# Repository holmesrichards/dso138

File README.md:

# DSO138 Oscilloscope

This is the JYE Tech DSO138 Oscilloscope put behind a 10 cm wide Kosmo format panel. 

Slide switches, tactile buttons, and trigger indicator LED are mounted to an auxiliary PCB mounted behind the panel. Also on this board are a Eurorack style 10-pin power header with 10 µF caps and power reversal diodes, and a 9 volt regulator and TL072 op amp with associated passive components.

A BNC jack and a 1/4" phone input jack are mounted on the front panel. A toggle switch selects whether the scope input is connected to the BNC or to the 1/4" jack signal after being buffered with the TL072. The latter signal, buffered, also goes to a second 1/4" panel mounted jack, so the signal can be passed on to another module.

Also on the front panel is another toggle switch, controlling the 9 V power. (It's good to power off the scope when not in use, for at least three reasons: the scope draws about 130 mA current on the +12 V rail, it probably puts out some digital noise you don't want getting into your synth sound, and leaving it powered off when not in use will help extend the life of the display.)

Connections to and from each slide switch are sent to the DSO138 switch footprints via an 8-conductor ribbon cable. A fourth ribbon cable connects the tactile buttons, both sides of the LED, and the input signal to the appropriate pads on the main board. Two more wires carry 9 V and ground to that board, which is mounted perpendicular to the front panel. I used a 3D printed carrier and long spacers to attach it.

The display PCB is mounted to the front panel and is connected to the main PCB via a 40 conductor ribbon cable.

## Current draw
130 mA +12 V, 10 mA -12 V

## Photos

## Documentation

* [Schematic (auxiliary board)](Docs/dso138.pdf)
* PCB layout: [front](Docs/dso138_layout_front.pdf), [back](Docs/dso138_layout_back.pdf)
* [BOM](Docs/dso138_bom.md)
* [Build notes](Docs/build.md)

## GitHub repository

* [https://github.com/holmesrichards/dso138](https://github.com/holmesrichards/dso138)

## Submodules

This repo uses submodules aoKicad and Kosmo_panel, which provide needed libaries for KiCad. To clone:

```
git clone git@github.com:holmesrichards/dso138.git
git submodule init
git submodule update
```

Alternatively do

```
git clone --recurse-submodules git@github.com:holmesrichards/dso138.git
```

Or if you download the repository as a zip file, you must also click on the "aoKicad" and "Kosmo\_panel" links on the GitHub page (they'll be in the Libraries folder and will have "@ something" after them) and download them as separate zip files which you can unzip into this repo's aoKicad and Kosmo\_panel directories (in the Libraries folder).

If desired, copy the files from aoKicad and Kosmo\_panel to wherever you prefer. 

Then in KiCad, go into Edit Symbols and add symbol libraries 

```
aoKicad/AO_symbols
Kosmo_panel/Kosmo
```
and go into Edit Footprints and add footprint libraries 
```
aoKicad/AO_tht
Kosmo_panel/Kosmo_panel.
```

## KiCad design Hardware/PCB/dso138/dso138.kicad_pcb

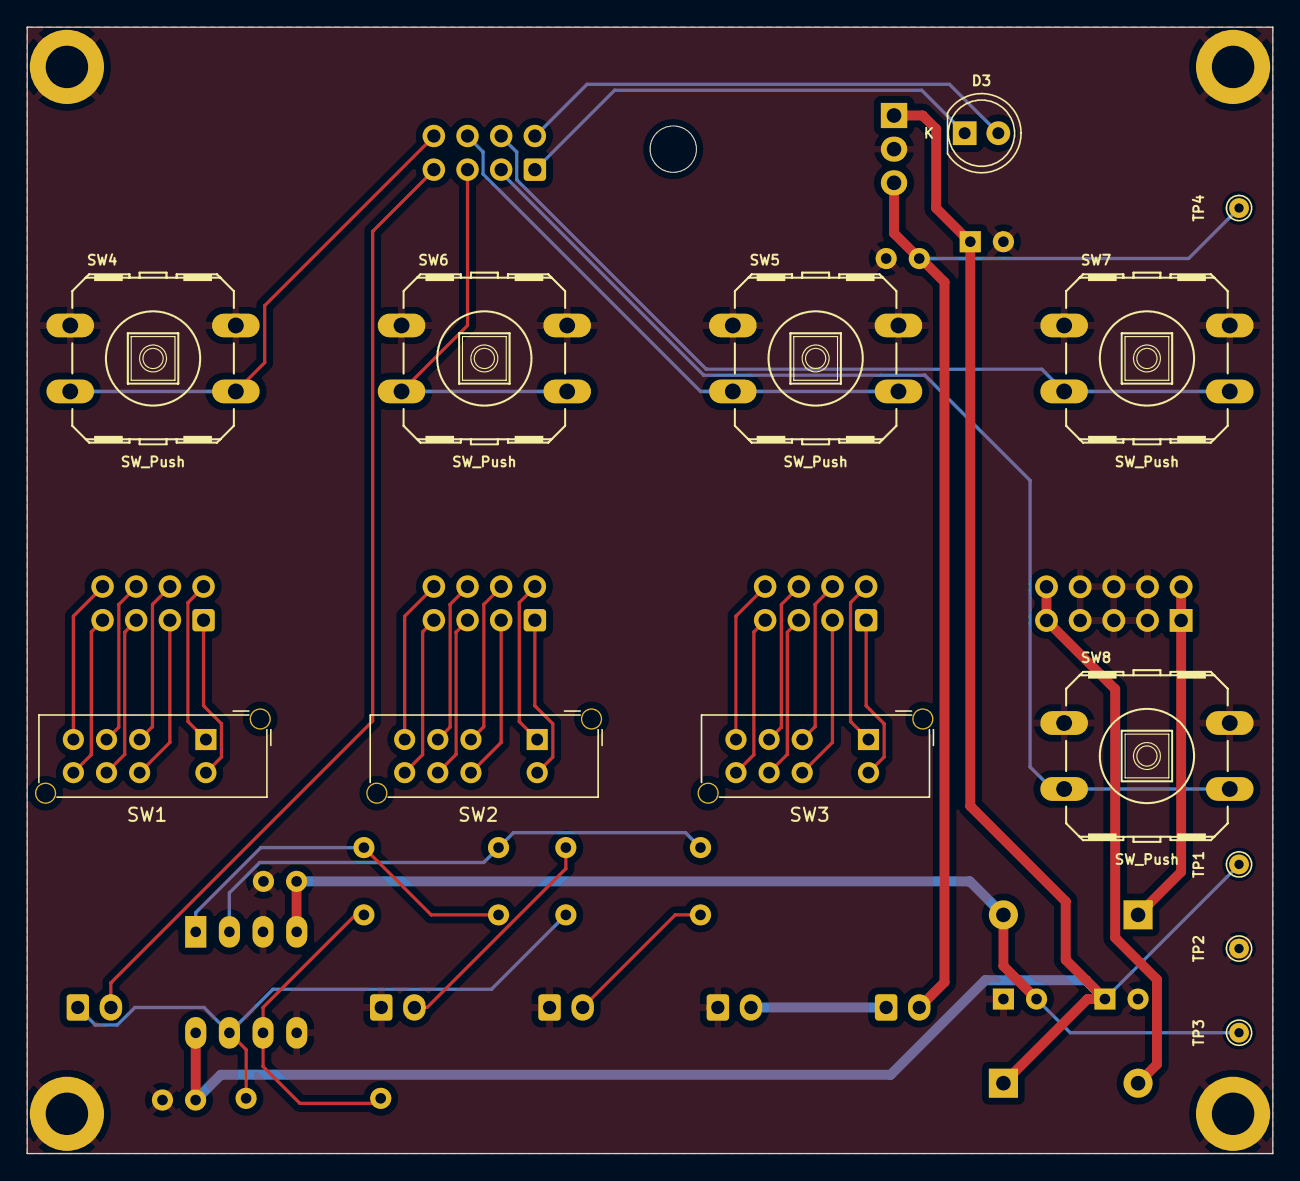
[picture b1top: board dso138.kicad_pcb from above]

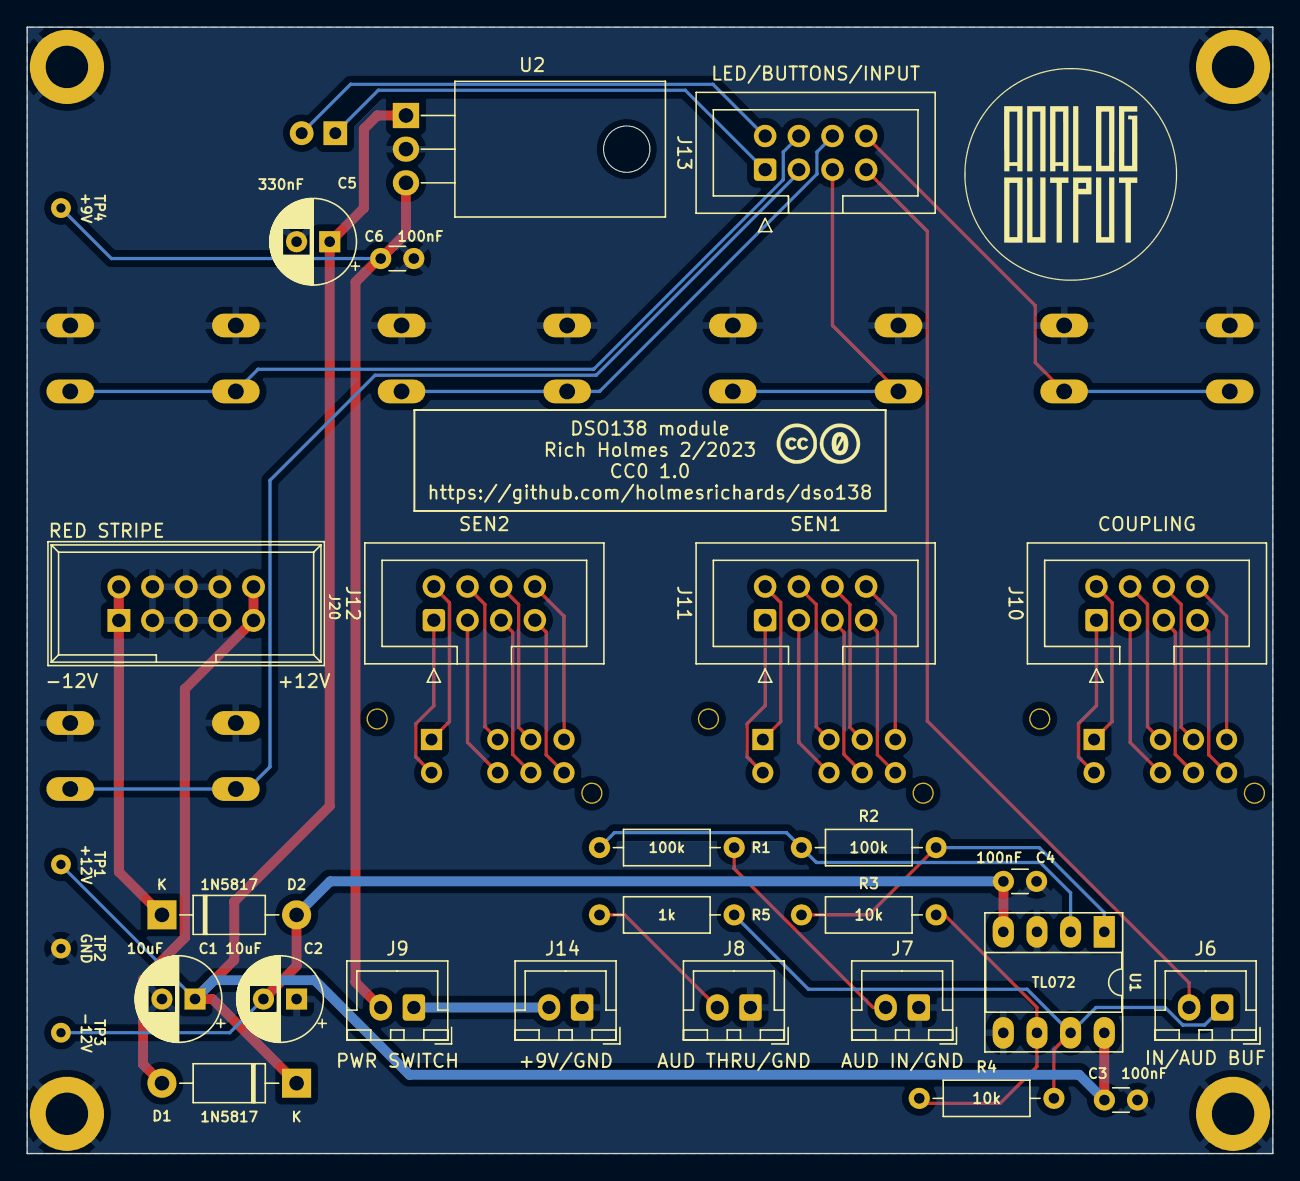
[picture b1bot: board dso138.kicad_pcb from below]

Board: 2 copper layers, 94.0 x 85.0 mm, 45 parts (27 on the bottom side), 45 nets.

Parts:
C1, C2: 10uF; CP_Radial_D6.3mm_P2.50mm
C3, C4, C6: 100nF; C_Disc_D3.0mm_W1.6mm_P2.50mm
C5: 330nF; CP_Radial_D6.3mm_P2.50mm
D1, D2: 1N5817; D_DO-41_SOD81_P10.16mm_Horizontal
D3: LED_green; LED_D5.0mm
GRAF1: Behind; dso138_behind
GRAF1#2: CC0 logo; CC0_logo
GRAF2: AO logo; analogoutput
H1, H2, H3, H4: MountingHole_with_pin; MountingHole_3.2mm_Pad
J6, J7, J8, J9, J14: Conn_01x02; JST_XH_B2B-XH-A_1x02_P2.50mm_Vertical
J10, J11, J12, J13: Conn_02x04_Odd_Even; IDC-Header_2x04_P2.54mm_Vertical
J20: Synth_power_2x5; Power_Header
R1, R2: 100k; R_Axial_DIN0207_L6.3mm_D2.5mm_P10.16mm_Horizontal
R3, R4: 10k; R_Axial_DIN0207_L6.3mm_D2.5mm_P10.16mm_Horizontal
R5: 1k; R_Axial_DIN0207_L6.3mm_D2.5mm_P10.16mm_Horizontal
SW1, SW2, SW3: SW_DP3T; SW_CK_OS203012MU5QP1_DP3T
SW4, SW5, SW6, SW7, SW8: SW_Push; Tactile_E-switch_TL1100F160Q
TP1: +12V; TestPoint_THTPad_D1.5mm_Drill0.7mm
TP2: GND; TestPoint_THTPad_D1.5mm_Drill0.7mm
TP3: -12V; TestPoint_THTPad_D1.5mm_Drill0.7mm
TP4: +9V; TestPoint_THTPad_D1.5mm_Drill0.7mm
U1: TL072; DIP-8_W7.62mm_Socket_LongPads
U2: LM7809_TO220; TO-220-3_Horizontal_TabDown

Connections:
+9V: C6.1, J9.2, TP4.1, U2.3 (VO)
+12V: C1.1, C3.1, C5.1, D1.1 (K), TP1.1, U1.8 (V+), U2.1 (VI)
-12V: C2.2, C4.2, D2.2 (A), TP3.1, U1.4 (V-)
/9V_SWITCHED: J9.1, J14.2
/AUDIO_BUF: J6.1, R4.2, R5.1, U1.7
/AUDIO_IN: J7.2, R1.1
/AUDIO_THROUGH: J8.2, R5.2
/Controls board/+12_IN: D1.2 (A), J20.9 (+12V), J20.10 (+12V)
/Controls board/-12_IN: D2.1 (K), J20.1 (-12V), J20.2 (-12V)
/INPUT: J6.2, J13.7
/LED_A: D3.2 (A), J13.2
/LED_K: D3.1 (K), J13.1
/SW_CPL_AC_A: J10.6, SW1.3
/SW_CPL_AC_B: J10.5, SW1.7
/SW_CPL_COMM_A: J10.4, SW1.2
/SW_CPL_COMM_B: J10.3, SW1.6
/SW_CPL_DC_A: J10.2, SW1.1
/SW_CPL_DC_B: J10.1, SW1.5
/SW_CPL_GND_A: J10.8, SW1.4
/SW_CPL_GND_B: J10.7, SW1.8
/SW_HOLDRUN: J13.8, SW4.2
/SW_MINUS: J13.5, SW6.2
/SW_PLUS: J13.6, SW5.2
/SW_RESET: J13.3, SW8.2
/SW_SELECT: J13.4, SW7.2
/SW_SEN1_1V_A: J11.8, SW2.4
/SW_SEN1_1V_B: J11.7, SW2.8
/SW_SEN1_10MV_A: J11.2, SW2.1
/SW_SEN1_10MV_B: J11.1, SW2.5
/SW_SEN1_100MV_A: J11.6, SW2.3
/SW_SEN1_100MV_B: J11.5, SW2.7
/SW_SEN1_COMM_A: J11.4, SW2.2
/SW_SEN1_COMM_B: J11.3, SW2.6
/SW_SEN2_COMM_A: J12.4, SW3.2
/SW_SEN2_COMM_B: J12.3, SW3.6
/SW_SEN2_X1_A: J12.2, SW3.1
/SW_SEN2_X1_B: J12.1, SW3.5
/SW_SEN2_X2_A: J12.6, SW3.3
/SW_SEN2_X2_B: J12.5, SW3.7
/SW_SEN2_X5_A: J12.8, SW3.4
/SW_SEN2_X5_B: J12.7, SW3.8
GND: C1.2, C2.1, C3.2, C4.1, C5.2, C6.2, H1.1, H2.1, H3.1, H4.1, J7.1, J8.1, J14.1, J20.3 (GND), J20.4 (GND), J20.5 (GND), J20.6 (GND), J20.7 (GND), J20.8 (GND), SW4.1, SW5.1, SW6.1, SW7.1, SW8.1, TP2.1, U1.3 (+), U1.5 (+), U2.2 (GND)
unnamed: R2.2, R3.1, U1.1
unnamed: R1.2, R2.1, U1.2 (-)
unnamed: R3.2, R4.1, U1.6 (-)

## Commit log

2022-11-12 Initial version
2022-11-27 Add power switch
2023-01-16 Panel
2023-02-05 KiCad 7; Reorg schematic and add panel components & connectors; re-enable 3D models
2023-02-05 Relocate image
2023-02-19 TO-220 regulator; panel
2023-02-20 Net classes, move 7809 and make horizontal, inverting buffers, power switch via PCB
2023-02-20 PDF docs
2023-02-20 README
2023-02-20 Mechanicals
2023-02-22 rm libraries
2023-02-22 gerbers
2023-02-22 libraries in new place
2023-03-06 STL file; BOM; documentation
2023-03-06 Space!
2023-03-06 BOM correction
